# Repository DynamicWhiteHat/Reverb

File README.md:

# Reverb
A custom record player. Place a disk and have it play. Original idea by AKZ Dev on YouTube.

## Features:
- ESP32 S3 Wroom 1 SoM
- 8Ω 10W Speaker
- Disks correspond to songs through an RFID reader
- Gesture sensor for touch-free volume control
- Working stylus that can start and stop music
- 3x8 audio visualizer array
- 2x USB out: 3.0 A at 5V

## Why I designed this project

I saw [this](https://www.youtube.com/watch?v=fBjv4E7mpA4) video on YouTube one day, and I wanted to make my own version. He used an RPi Zero with other modules. I decided that I wanted to improve on this design by making a custom ESP32-based PCB, a built in speaker, and other small features. I also found another video about an ESP32 speaker with an audio visualizer, so I decided to add that through a 3x8 neopixel array. I have gotten better at routing PCBs as a result of this project, and I have also gained a sense of how to make good-looking PCB layouts.

## Image gallery:
<table align="center">
  <tr>
    <td align="center">
      
    </td>
    <td align="center">
      
    </td>
  </tr>
  <tr>
    <td align="center" colspan="2">
      
    </td>
  </tr>
</table>

## Schematic, PCB, And Layout
<table align="center">
  <tr>
    <td align="center" colspan="2">
      
    </td>
  </tr>
  <tr>
    <td align="center">
      
    </td>
    <td align="center">
      
    </td>
  </tr>
  <tr>
    <td align="center" colspan="2">
      
    </td>
  </tr>
  <tr>
    <td align="center" colspan="2">
     
    </td>
  </tr>
</table>

## How It Works
The main control board is based on an ESP32-S3 Wroom 1, which is Wifi and Bluetooth enabled. This allows me to connect the SoM to my phone or other device running Spotify. Using the web API, I can control music that plays from my device. Reverb also uses a MAX98357A I2S amplifier that is wired to an 8Ω 10W speaker, allowing audio playback from the music player instead of the device. Additionally, a 3x8 SK6812 Mini NeoPixel array is mounted on the front of the case with a thin wall, allowing audio playback to be visualized. The PAJ7620U2 gesture sensor, located under the REVERB logo on the case, can detect gestures to increase or decrease volume, skip tracks, and perform other tasks. Finally, the main component in the whole design is the RC522 RFID sensor, which picks up data from the RFID stickers located within the 3D printed disks. This allows each disk to be mapped to a song, allowing playback that feels real.

## Bill Of Materials
| Item                      | Quantity     | Link                                                                                   | Price  | Comment                                            |
|---------------------------|--------------|----------------------------------------------------------------------------------------|--------|----------------------------------------------------|
| JLCPCB Order              | 1            | Quote                                                                                  | $23.62 | PCB+Stencil                                        |
| LCSC Order                | 1            | See LCSC BOM                                                                           | $28.00 | PCB Parts                                          |
| Stepper Motor             | 1            | https://www.aliexpress.us/item/2251832816516054.html                                   | $2.61  |                                                    |
| RC522 RFID Reader         | 1            | https://www.aliexpress.us/item/3256805262944828.html                                   | $1.46  |                                                    |
| RFID Tag                  | 1 Pack of 30 | https://www.aliexpress.us/item/3256807346917359.html                                   | $2.92  |                                                    |
| PAJ7620U2 Gesture Sensor  | 1            | https://www.aliexpress.us/item/3256803918726745.html                                   | $5.09  |                                                    |
| Speaker                   | 1            | https://www.aliexpress.us/item/3256806860528919.html                                   | $8.12  |                                                    |
| Power Switch              | 1 Pack of 5  | https://www.aliexpress.us/item/3256803938436290.html                                   | $2.12  |                                                    |
| SD Card Reader            | 1            | https://www.aliexpress.us/item/3256805115720436.html                                   | $0.83  |                                                    |
| US5881 Hall Effect Sensor | 1 Pack of 10 | https://www.aliexpress.us/item/3256806135616417.html                                   | $1.82  |                                                    |
| M2-M5 Screw Set           | 1            | https://www.amazon.com/mxuteuk-Assortment-Machine-Washers-Printing/dp/B0FM3G5K6H/?th=1 | $9.99  | From Amazon as AliExpress doesn't sell assortments |
|                           |              |                                                                                        | $86.58 |                                                    |

### LCSC Bill Of Materials
| LCSC                                                                                                    |                 |                       |                    |                 |                |          |                                                   |
|---------------------------------------------------------------------------------------------------------|-----------------|-----------------------|--------------------|-----------------|----------------|----------|---------------------------------------------------|
| Description                                                                                             | Quantity Needed | Mrf#                  | Minimum Order Qty. | Unit Price(USD) | Ext.Price(USD) | LCSC#    | Product Link                                      |
| 100nF ±10% 50V Ceramic Capacitor X7R 0603                                                               |              28 | CC0603KRX7R9BB104     |                100 |          0.0021 |           0.21 | C14663   | https://www.lcsc.com/product-detail/C14663.html   |
| 10kΩ ±1% 100mW 0603 Thick Film Resistor                                                                 |               3 | 0603WAF1002T5E        |                100 |          0.0011 |           0.11 | C25804   | https://www.lcsc.com/product-detail/C25804.html   |
| 10uF ±10% 10V Ceramic Capacitor X5R 0603                                                                |               5 | CL10A106KP8NNNC       |                 50 |          0.0065 |           0.33 | C19702   | https://www.lcsc.com/product-detail/C19702.html   |
| 1MΩ ±1% 100mW 0603 Thick Film Resistor                                                                  |               2 | 0603WAF1004T5E        |                100 |          0.0011 |           0.11 | C22935   | https://www.lcsc.com/product-detail/C22935.html   |
| Diode Independent 40V 1A Surface Mount SOD-123                                                          |               1 | K1N5819HW-7-F         |                 50 |          0.0133 |           0.67 | C2891704 | https://www.lcsc.com/product-detail/C2891704.html |
| 1kΩ ±1% 100mW 0603 Thick Film Resistor                                                                  |               1 | 0603WAF1001T5E        |                100 |          0.0012 |           0.12 | C21190   | https://www.lcsc.com/product-detail/C21190.html   |
| 1uF ±10% 50V Ceramic Capacitor X5R 0603                                                                 |               1 | CL10A105KB8NNNC       |                 50 |          0.0056 |           0.28 | C15849   | https://www.lcsc.com/product-detail/C15849.html   |
| 22uF ±20% 6.3V Ceramic Capacitor X5R 0603                                                               |               1 | CL10A226MQ8NRNC       |                 20 |          0.0094 |           0.19 | C59461   | https://www.lcsc.com/product-detail/C59461.html   |
| 4.7kΩ ±1% 100mW 0603 Thick Film Resistor                                                                |               4 | 0603WAF4701T5E        |                100 |          0.0011 |           0.11 | C23162   | https://www.lcsc.com/product-detail/C23162.html   |
| 4.7uF ±10% 16V Ceramic Capacitor X5R 0603                                                               |               2 | CL10A475KO8NNNC       |                 10 |          0.0102 |           0.10 | C19666   | https://www.lcsc.com/product-detail/C19666.html   |
| 5.1kΩ ±1% 100mW 0603 Thick Film Resistor                                                                |               2 | 0603WAF5101T5E        |                100 |          0.0011 |           0.11 | C23186   | https://www.lcsc.com/product-detail/C23186.html   |
| 634kΩ ±1% 100mW 0603 Thick Film Resistor                                                                |               1 | 0603WAF6343T5E        |                100 |          0.0007 |           0.07 | C65831   | https://www.lcsc.com/product-detail/C65831.html   |
| 6V Positive Fixed 3.3V SOT-223 Voltage Regulators - Linear, Low Drop Out (LDO) Regulators RoHS          |               1 | AP7361C-33E-13        |                  5 |          0.2779 |           1.39 | C500795  | https://www.lcsc.com/product-detail/C500795.html  |
| Diode Array 1 Pair Common Cathode 30V 200mA Surface Mount SOT-23                                        |               1 | BAT54C                |                 50 |          0.0095 |           0.48 | C727125  | https://www.lcsc.com/product-detail/C727125.html  |
| Connector Header 2 position 2mm Pitch 2A Right Angle -25℃~+85℃                                          |               1 | S2B-PH-K-S(LF)(SN)    |                 20 |          0.0355 |           0.71 | C173752  | https://www.lcsc.com/product-detail/C173752.html  |
| Connector Header 5 position 2.5mm Pitch 3A Through Hole -25℃~+85℃                                       |               1 | B5B-XH-A(LF)(SN)      |                  5 |          0.0826 |           0.41 | C157991  | https://www.lcsc.com/product-detail/C157991.html  |
| 2.4GHz ESP32-S3 Chip On-board PCB Antenna -98.2dBm SMD,25.5x18mm RF Transceiver Modules and Modems RoHS |               1 | ESP32-S3-WROOM-1-N8R8 |                  1 |          4.9347 |           4.93 | C2913201 | https://www.lcsc.com/product-detail/C2913201.html |
| Class D TQFN-16-EP(3x3) Audio Amplifiers RoHS                                                           |               1 | MAX98357AETE+T        |                  1 |          1.3216 |           1.32 | C910544  | https://www.lcsc.com/product-detail/C910544.html  |
| SMD-4P,3.7x3.5mm LED Addressable, Specialty RoHS                                                        |              24 | SK6812SMINI           |                 30 |          0.0617 |           1.85 | C7423118 | https://www.lcsc.com/product-detail/C7423118.html |
| Tactile Switch SPST 160gf 2mm SMD (SMT) Tab 4mm x 3mm Surface Mount                                     |               2 | TS-1088-AR02016       |                 10 |          0.0426 |           0.43 | C720477  | https://www.lcsc.com/product-detail/C720477.html  |
| Lithium-ion/Polymer ESOP-8                                                                              |               1 | TP4056                |                  5 |           0.091 |           0.46 | C382139  | https://www.lcsc.com/product-detail/C382139.html  |
| 50V 500mA SOIC-16 Bipolar Transistor Arrays RoHS                                                        |               1 | ULN2003ADR            |                  5 |          0.1121 |           0.56 | C7512    | https://www.lcsc.com/product-detail/C7512.html    |
| USB-C (USB TYPE-C) Receptacle Connector 6 Position Surface Mount                                        |               2 | TYPE-C-31-M-17        |                  5 |          0.1789 |           0.89 | C283540  | https://www.lcsc.com/product-detail/C283540.html  |
| USB-C (USB TYPE-C) Receptacle Connector 16 Position Surface Mount                                       |               1 | TYPE-C-31-M-12        |                  5 |          0.1908 |           0.95 | C165948  | https://www.lcsc.com/product-detail/C165948.html  |
| 5kΩ Thin Film Resistor ±25ppm/℃ ±0.1% 0603 Chip Resistor - Surface Mount RoHS                           |               1 | TR0603B5K00P0525Z     |                 20 |           0.028 |           0.56 | C3202451 | https://www.lcsc.com/product-detail/C3202451.html |
| 400mΩ ±1% 100mW 0603 Thick Film Resistor                                                                |               1 | FRL0603FR400TS        |                100 |          0.0035 |           0.35 | C5126047 | https://www.lcsc.com/product-detail/C5126047.html |
|                                                                                                         |                 |                       |                    | Combined Price  |         $18.23 |          |                                                   |
|                                                                                                         |                 |                       |                    | Shipping        |          $9.99 |          |                                                   |
|                                                                                                         |                 |                       |                    | Total Price     |         $27.68 |          |                                                   |

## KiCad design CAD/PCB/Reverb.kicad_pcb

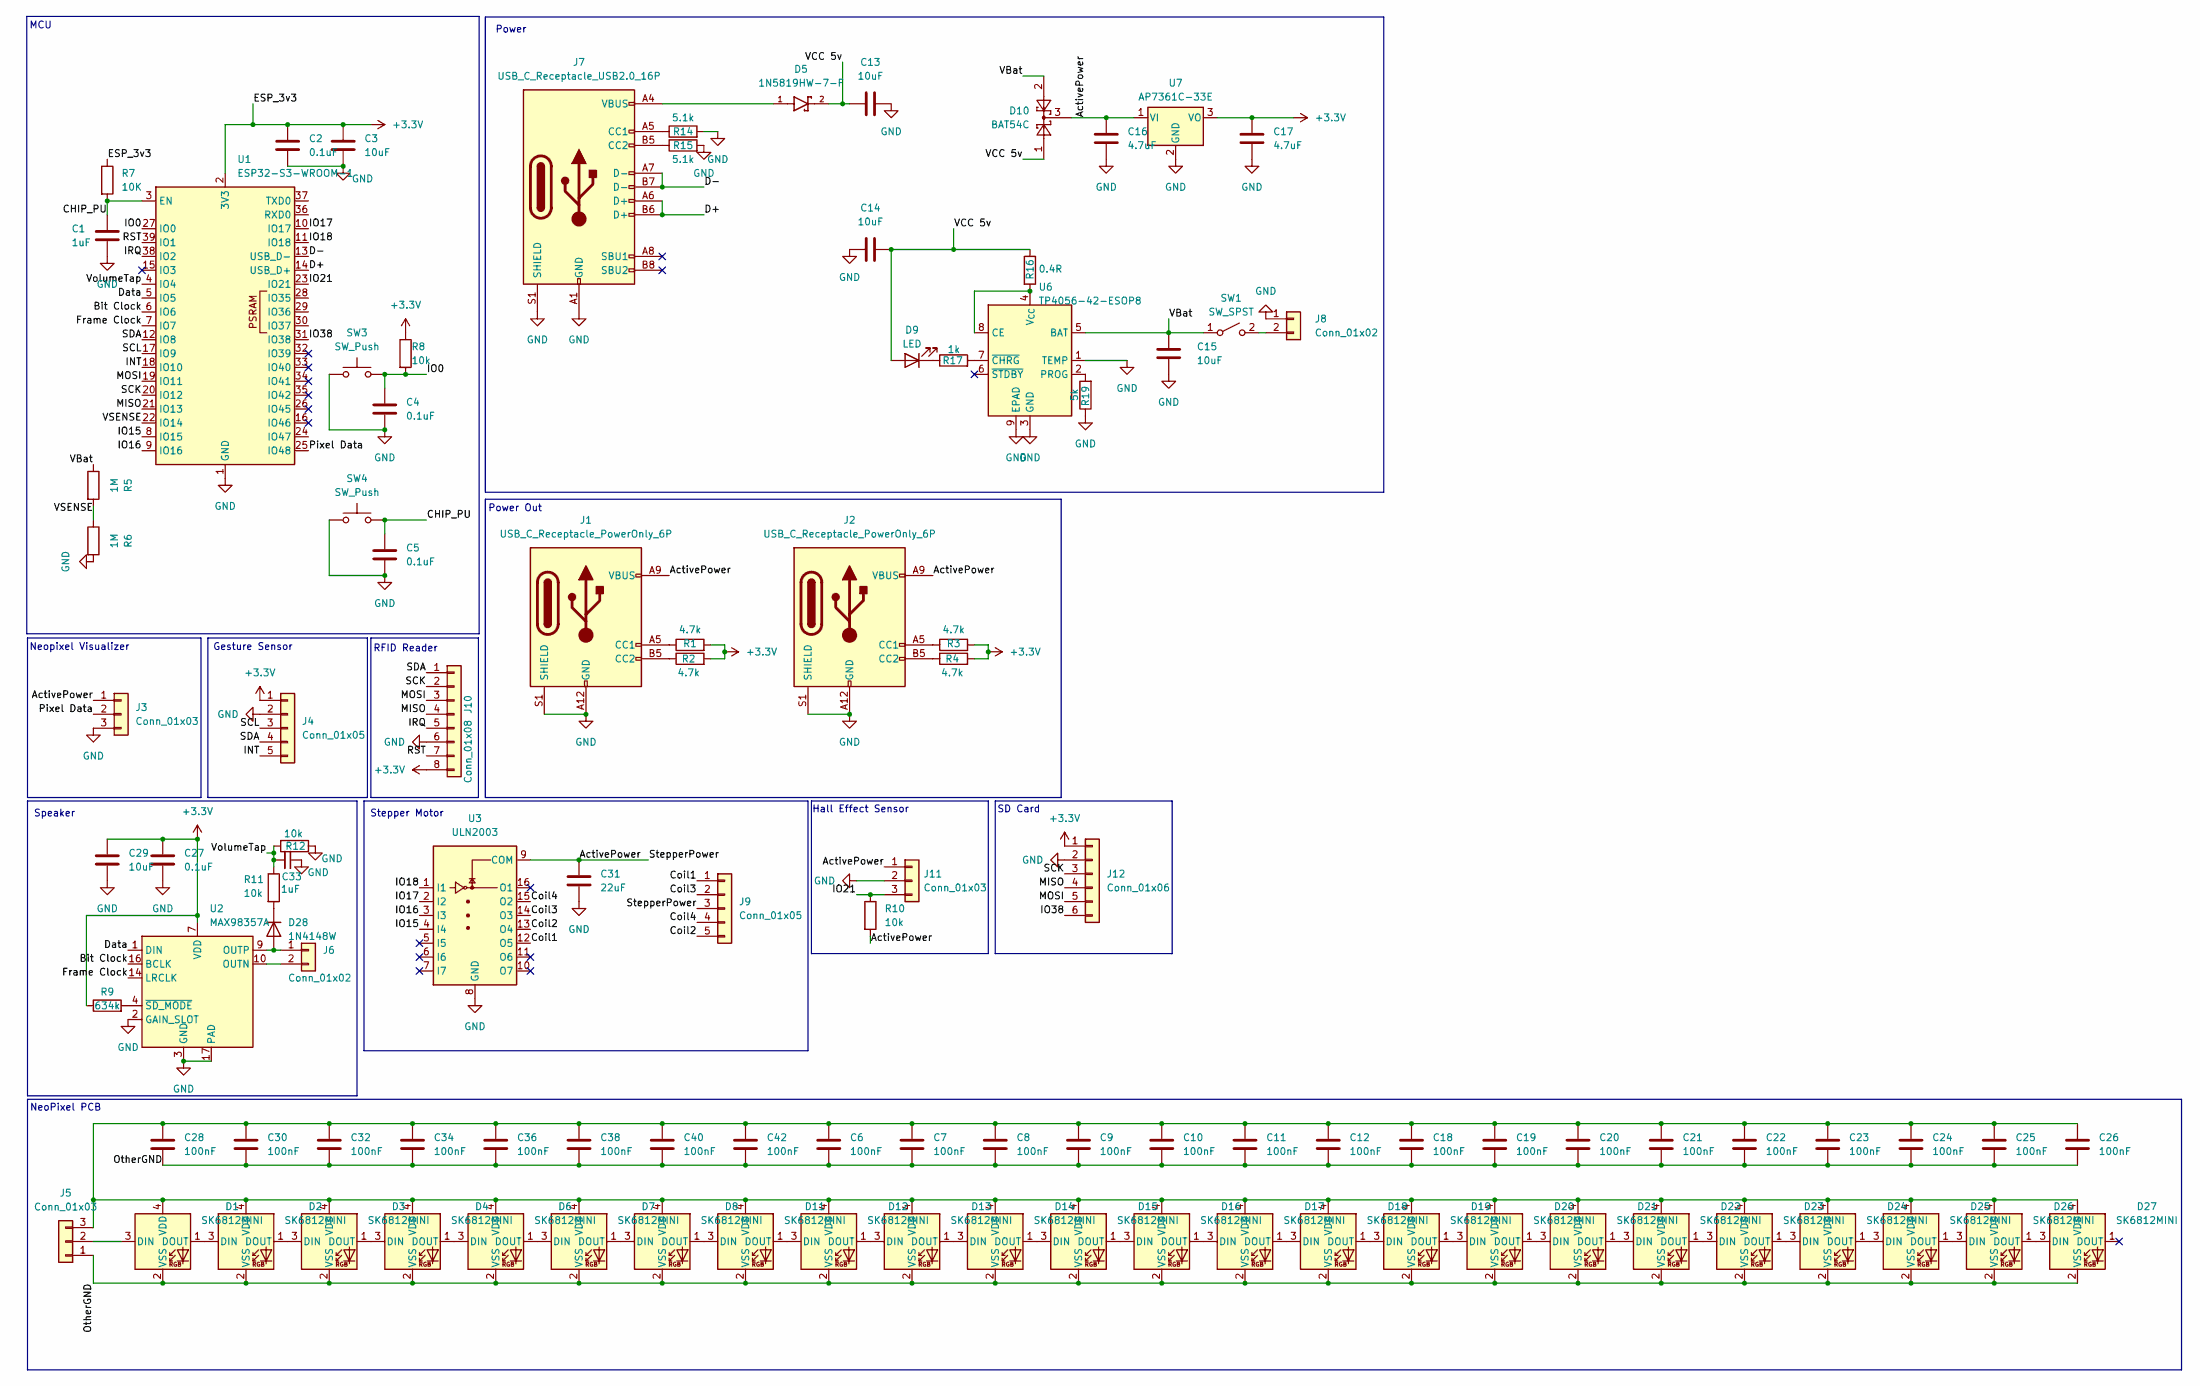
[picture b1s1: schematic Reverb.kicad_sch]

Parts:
C1, C33: 1uF; C_0603_1608Metric
C2, C4, C5, C27: 0.1uF; C_0603_1608Metric
C3, C13, C14, C15, C29: 10uF; C_0603_1608Metric
C6, C7, C8, C9, C10, C11, C12, C18, C19, C20, C21, C22, C23, C24, C25, C26, C28, C30, C32, C34, C36, C38, C40, C42: 100nF; C_0603_1608Metric
C16, C17: 4.7uF; C_0603_1608Metric
C31: 22uF; C_0603_1608Metric
D1, D2, D3, D4, D6, D7, D8, D11, D12, D13, D14, D15, D16, D17, D18, D19, D20, D21, D22, D23, D24, D25, D26, D27: SK6812MINI; LED_SK6812MINI_PLCC4_3.5x3.5mm_P1.75mm
D5: 1N5819HW-7-F; D_SOD-123; PARTREV 18-2
D9: LED; LED_0603_1608Metric
D10: BAT54C; SOT-23
D28: 1N4148W; D_SOD-123
J1, J2: USB_C_Receptacle_PowerOnly_6P; USB_C_Receptacle_HRO_TYPE-C-31-M-17
J3, J5: Conn_01x03; PinHeader_1x03_P2.54mm_Vertical
J4: Conn_01x05; PinHeader_1x05_P2.54mm_Vertical
J6: Conn_01x02; PinHeader_1x02_P2.54mm_Vertical
J7: USB_C_Receptacle_USB2.0_16P; USB_C_Receptacle_HRO_TYPE-C-31-M-12
J8: Conn_01x02; JST_PH_S2B-PH-K_1x02_P2.00mm_Horizontal
J9: Conn_01x05; JST_XH_B5B-XH-AM_1x05_P2.50mm_Vertical
J10: Conn_01x08; PinHeader_1x08_P2.54mm_Vertical
J11: Conn_01x03; PinSocket_1x03_P2.54mm_Vertical
J12: Conn_01x06; 6PinTestPoint_Pad_2.0x2.0mm
R1, R2, R3, R4: 4.7k; R_0603_1608Metric
R5, R6: 1M; R_0603_1608Metric
R7: 10K; R_0603_1608Metric
R8, R10, R11, R12: 10k; R_0603_1608Metric
R9: 634k; R_0603_1608Metric
R14, R15: 5.1k; R_0603_1608Metric
R16: 0.4R; R_0603_1608Metric
R17: 1k; R_0603_1608Metric
R19: 5k; R_0603_1608Metric
SW1: SW_SPST; PinHeader_1x02_P2.54mm_Vertical
SW3, SW4: SW_Push; SW_TS-1088-AR02016
U1: ESP32-S3-WROOM-1
U2: MAX98357A; TQFN-16-1EP_3x3mm_P0.5mm_EP1.23x1.23mm
U3: ULN2003; SOIC-16_3.9x9.9mm_P1.27mm
U6: TP4056-42-ESOP8; SOIC-8-1EP_3.9x4.9mm_P1.27mm_EP2.41x3.3mm_ThermalVias
U7: AP7361C-33E; SOT-223-3_TabPin2

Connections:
+3.3V: C2.1, C3.1, C17.1, C27.1, C29.1, J4.1, J10.8, J12.1, R1.2, R2.2, R3.2, R4.2, R7.1, R8.1, R9.1, U1.2 (3V3), U2.7 (VDD), U2.8 (VDD), U7.3 (VO)
/ActivePower: C16.1, C31.1, D10.3, J1.A9 (VBUS), J1.B9 (VBUS), J2.A9 (VBUS), J2.B9 (VBUS), J3.1, J9.3, J11.1, R10.2, U3.9 (COM), U7.1 (VI)
/Bit Clock: U1.6 (IO6), U2.16 (BCLK)
/CHIP_PU: C1.1, C5.1, R7.2, SW4.2, U1.3 (EN)
/Coil1: J9.1, U3.12 (O5)
/Coil2: J9.5, U3.13 (O4)
/Coil3: J9.2, U3.14 (O3)
/Coil4: J9.4, U3.15 (O2)
/D+: J7.A6 (D+), J7.B6 (D+), U1.14 (USB_D+)
/D-: J7.A7 (D-), J7.B7 (D-), U1.13 (USB_D-)
/Data: U1.5 (IO5), U2.1 (DIN)
/Frame Clock: U1.7 (IO7), U2.14 (LRCLK)
/INT: J4.5, U1.18 (IO10)
/IO0: C4.1, R8.2, SW3.2, U1.27 (IO0)
/IO15: U1.8 (IO15), U3.4 (I4)
/IO16: U1.9 (IO16), U3.3 (I3)
/IO17: U1.10 (IO17), U3.2 (I2)
/IO18: U1.11 (IO18), U3.1 (I1)
/IO21: J11.3, R10.1, U1.23 (IO21)
/IO38: J12.6, U1.31 (IO38)
/IRQ: J10.5, U1.38 (IO2)
/MISO: J10.4, J12.4, U1.21 (IO13)
/MOSI: J10.3, J12.5, U1.19 (IO11)
/OtherGND: C6.2, C7.2, C8.2, C9.2, C10.2, C11.2, C12.2, C18.2, C19.2, C20.2, C21.2, C22.2, C23.2, C24.2, C25.2, C26.2, C28.2, C30.2, C32.2, C34.2, C36.2, C38.2, C40.2, C42.2, D1.2 (VSS), D2.2 (VSS), D3.2 (VSS), D4.2 (VSS), D6.2 (VSS), D7.2 (VSS), D8.2 (VSS), D11.2 (VSS), D12.2 (VSS), D13.2 (VSS), D14.2 (VSS), D15.2 (VSS), D16.2 (VSS), D17.2 (VSS), D18.2 (VSS), D19.2 (VSS), D20.2 (VSS), D21.2 (VSS), D22.2 (VSS), D23.2 (VSS), D24.2 (VSS), D25.2 (VSS), D26.2 (VSS), D27.2 (VSS), J5.1
/Pixel Data: J3.2, U1.25 (IO48)
/RST: J10.7, U1.39 (IO1)
/SCK: J10.2, J12.3, U1.20 (IO12)
/SCL: J4.3, U1.17 (IO9)
/SDA: J4.4, J10.1, U1.12 (IO8)
/VBat: C15.1, D10.2, R5.1, SW1.1 (A), U6.5 (BAT)
/VCC 5v: C13.1, C14.2, D5.2, D9.2 (A), D10.1, R16.1
/VSENSE: R5.2, R6.1, U1.22 (IO14)
/VolumeTap: C33.2, R11.1, R12.2, U1.4 (IO4)
GND: C1.2, C2.2, C3.2, C4.2, C5.2, C13.2, C14.1, C15.2, C16.2, C17.2, C27.2, C29.2, C31.2, C33.1, J1.A12 (GND), J1.B12 (GND), J1.S1 (SHIELD), J2.A12 (GND), J2.B12 (GND), J2.S1 (SHIELD), J3.3, J4.2, J7.A1 (GND), J7.A12 (GND), J7.B1 (GND), J7.B12 (GND), J7.S1 (SHIELD), J8.1, J10.6, J11.2, J12.2, R6.2, R12.1, R14.2, R15.2, R19.1, SW3.1, SW4.1, U1.1 (GND), U1.40 (GND), U1.41 (GND), U2.2 (GAIN_SLOT), U2.3 (GND), U2.11 (GND), U2.15 (GND), U2.17 (PAD), U3.8 (GND), U6.1 (TEMP), U6.3 (GND), U6.9 (EPAD), U7.2 (GND)
unnamed: D1.3 (DIN), J5.2
unnamed: D1.1 (DOUT), D2.3 (DIN)
unnamed: C6.1, C7.1, C8.1, C9.1, C10.1, C11.1, C12.1, C18.1, C19.1, C20.1, C21.1, C22.1, C23.1, C24.1, C25.1, C26.1, C28.1, C30.1, C32.1, C34.1, C36.1, C38.1, C40.1, C42.1, D1.4 (VDD), D2.4 (VDD), D3.4 (VDD), D4.4 (VDD), D6.4 (VDD), D7.4 (VDD), D8.4 (VDD), D11.4 (VDD), D12.4 (VDD), D13.4 (VDD), D14.4 (VDD), D15.4 (VDD), D16.4 (VDD), D17.4 (VDD), D18.4 (VDD), D19.4 (VDD), D20.4 (VDD), D21.4 (VDD), D22.4 (VDD), D23.4 (VDD), D24.4 (VDD), D25.4 (VDD), D26.4 (VDD), D27.4 (VDD), J5.3
unnamed: D2.1 (DOUT), D3.3 (DIN)
unnamed: D3.1 (DOUT), D4.3 (DIN)
unnamed: D4.1 (DOUT), D6.3 (DIN)
unnamed: D5.1, J7.A4 (VBUS), J7.A9 (VBUS), J7.B4 (VBUS), J7.B9 (VBUS)
unnamed: D6.1 (DOUT), D7.3 (DIN)
unnamed: D7.1 (DOUT), D8.3 (DIN)
unnamed: D9.1 (K), R17.1
unnamed: D8.1 (DOUT), D11.3 (DIN)
unnamed: D11.1 (DOUT), D12.3 (DIN)
unnamed: D12.1 (DOUT), D13.3 (DIN)
unnamed: D13.1 (DOUT), D14.3 (DIN)
unnamed: D14.1 (DOUT), D15.3 (DIN)
unnamed: D15.1 (DOUT), D16.3 (DIN)
unnamed: D16.1 (DOUT), D17.3 (DIN)
unnamed: D17.1 (DOUT), D18.3 (DIN)
unnamed: D18.1 (DOUT), D19.3 (DIN)
unnamed: D19.1 (DOUT), D20.3 (DIN)
unnamed: D20.1 (DOUT), D21.3 (DIN)
unnamed: D21.1 (DOUT), D22.3 (DIN)
unnamed: D22.1 (DOUT), D23.3 (DIN)
unnamed: D23.1 (DOUT), D24.3 (DIN)
unnamed: D24.1 (DOUT), D25.3 (DIN)
unnamed: D25.1 (DOUT), D26.3 (DIN)
unnamed: D26.1 (DOUT), D27.3 (DIN)
unnamed: D28.2 (A), J6.1, U2.9 (OUTP)
unnamed: D28.1 (K), R11.2
unnamed: J1.A5 (CC1), R1.1
unnamed: J1.B5 (CC2), R2.1
unnamed: J2.A5 (CC1), R3.1
unnamed: J2.B5 (CC2), R4.1
unnamed: J6.2, U2.10 (OUTN)
unnamed: J7.A5 (CC1), R14.1
unnamed: J7.B5 (CC2), R15.1
unnamed: J8.2, SW1.2 (B)
unnamed: R9.2, U2.4 (~SD_MODE)
unnamed: R16.2, U6.4 (V_{CC}), U6.8 (CE)
unnamed: R19.2, U6.2 (PROG)
unnamed: R17.2, U6.7 (~CHRG)

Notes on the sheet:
Neopixel Visualizer
Power Out
SD Card
NeoPixel PCB
MCU
Stepper Motor
Power
Hall Effect Sensor
Speaker
RFID Reader
Gesture Sensor

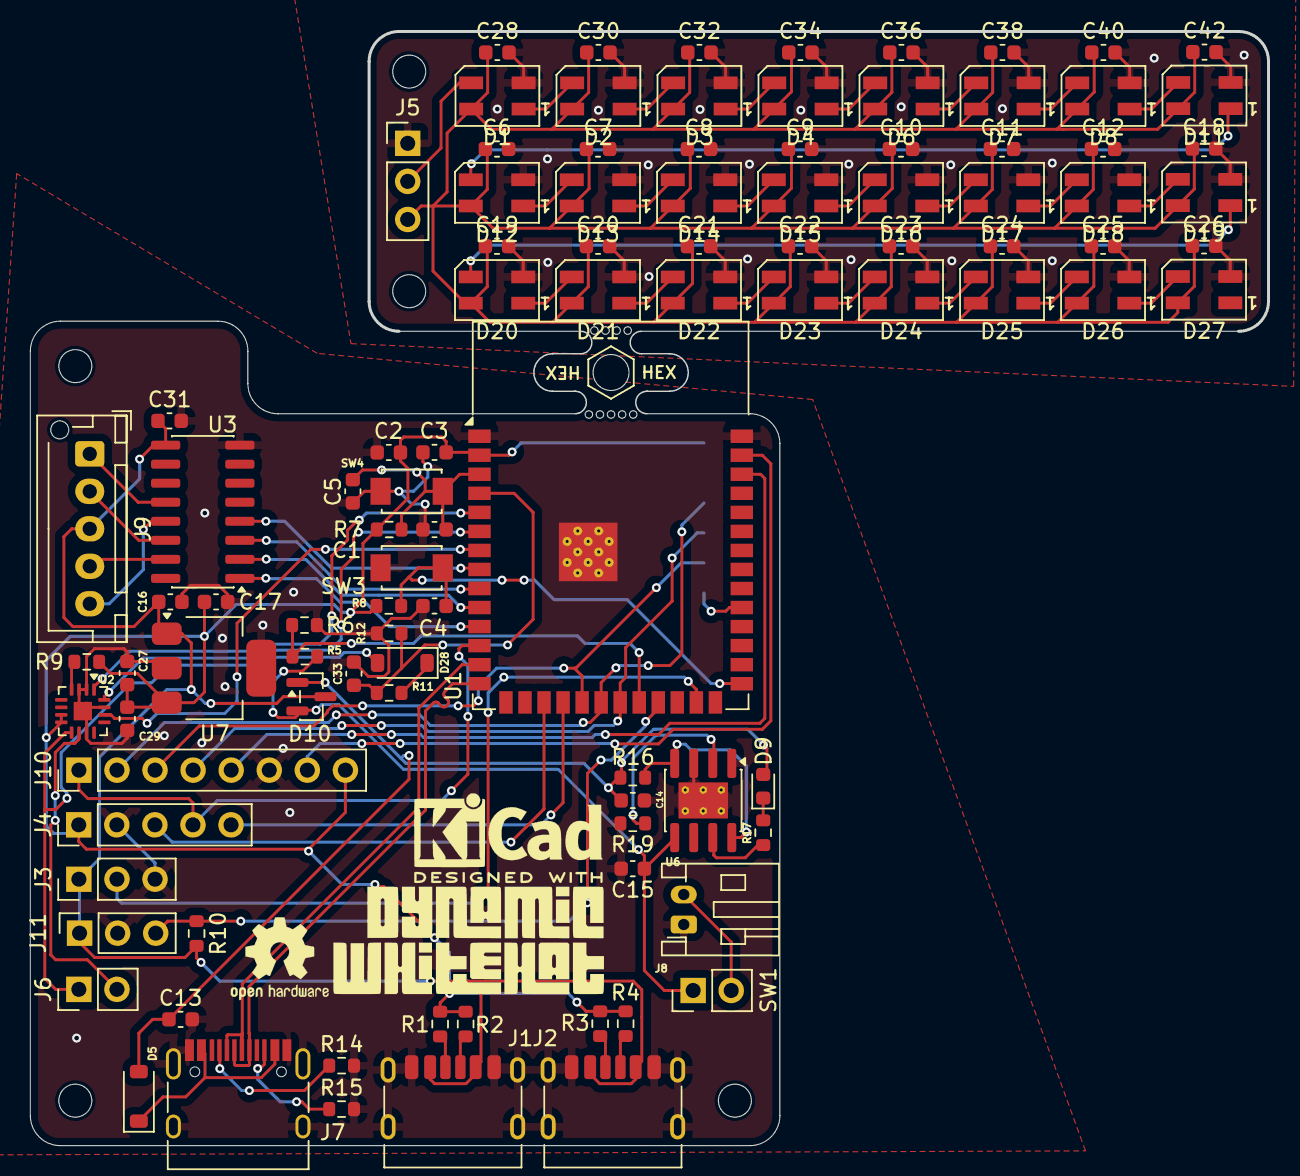
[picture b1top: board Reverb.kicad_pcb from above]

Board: 2 copper layers, 82.5 x 74.2 mm, 104 parts (1 on the bottom side), 75 nets.

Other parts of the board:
MB5: 5.5mm; mousebites_5p5mm_easysnap

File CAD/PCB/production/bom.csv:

Designator,Footprint,Quantity,Value,LCSC Part #
C1,0603,1,1uF,C15849
"C10, C11, C12, C18, C19, C20, C21, C22, C23, C24, C25, C26, C28, C30, C32, C34, C36, C38, C40, C42, C6, C7, C8, C9",0603,24,100nF,C14663
"C13, C14, C15, C29, C3",0603,5,10uF,C19702
"C16, C17",0603,2,4.7uF,C19666
"C2, C27, C4, C5",0603,4,0.1uF,C14663
C31,0603,1,22uF,C59461
C33,0603,1,1uF,
"D1, D11, D12, D13, D14, D15, D16, D17, D18, D19, D2, D20, D21, D22, D23, D24, D25, D26, D27, D3, D4, D6, D7, D8",LED_SK6812MINI_PLCC4_3.5x3.5mm_P1.75mm,24,SK6812MINI,C7423118
D10,SOT-23,1,BAT54C,C727125
D28,D_SOD-123,1,1N4148W,
D5,D_SOD-123,1,1N5819HW-7-F,C2891704
D9,0603,1,LED,C2286
"J1, J2",USB_C_Receptacle_HRO_TYPE-C-31-M-17,2,USB_C_Receptacle_PowerOnly_6P,C283540
J10,PinHeader_1x08_P2.54mm_Vertical,1,Conn_01x08,
J11,PinSocket_1x03_P2.54mm_Vertical,1,Conn_01x03,
J12,6PinTestPoint_Pad_2.0x2.0mm,1,Conn_01x06,
"J3, J5",PinHeader_1x03_P2.54mm_Vertical,2,Conn_01x03,
J4,PinHeader_1x05_P2.54mm_Vertical,1,Conn_01x05,
J6,PinHeader_1x02_P2.54mm_Vertical,1,Conn_01x02,
J7,USB_C_Receptacle_HRO_TYPE-C-31-M-12,1,USB_C_Receptacle_USB2.0_16P,C9900184415
J8,JST_PH_S2B-PH-K_1x02_P2.00mm_Horizontal,1,Conn_01x02,C173752
J9,JST_XH_B5B-XH-AM_1x05_P2.50mm_Vertical,1,Conn_01x05,C157991
"R1, R2, R3, R4",0603,4,4.7k,C23162
"R10, R7, R8",0603,3,10k,C25804
"R11, R12",0603,2,10k,
"R14, R15",0603,2,5.1k,C23186
R16,0603,1,0.4R,
R17,0603,1,1k,C21190
R19,0603,1,5k,
"R5, R6",0603,2,1M,C22935
R9,0603,1,634k,C65831
SW1,PinHeader_1x02_P2.54mm_Vertical,1,SW_SPST,
"SW3, SW4",SW_TS-1088-AR02016,2,SW_Push,C720477
U1,ESP32-S3-WROOM-1,1,ESP32-S3-WROOM-1,C2913198
U2,TQFN-16-1EP_3x3mm_P0.5mm_EP1.23x1.23mm,1,MAX98357A,C910544
U3,SOIC-16_3.9x9.9mm_P1.27mm,1,ULN2003,C7512
U6,SOIC-8-1EP_3.9x4.9mm_P1.27mm_EP2.41x3.3mm_ThermalVias,1,TP4056-42-ESOP8,C382139
U7,SOT-223-3_TabPin2,1,AP7361C-33E,C500795

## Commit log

2026-01-24 Added files
2026-01-24 Added images
2026-01-24 Added Back
2026-01-24 Made transparent files
2026-01-24 Update Reverb1T.png asset
2026-01-24 Update README with project details and BOM
    Expanded project description, added features, and included bill of materials with links and prices.
2026-01-24 Update BOM prices and ESP32 chip details
    Updated prices for LCSC order items and corrected ESP32 chip reference.
2026-01-24 Update prices and add new items in BOM
2026-01-24 Added code
2026-01-24 Revise quantities and prices in README BOM
    Updated quantities and prices for several components in the BOM.
2026-01-24 Adjust prices and quantities in Reverb BOM
    Updated prices for Power Switch, SD Card Reader, and US5881 Hall Effect Sensor.
2026-01-25 Update LCSC order details in README
    Updated LCSC order prices and quantities in the Bill of Materials section.
2026-01-25 Revise component prices and totals in BOM
    Updated prices and quantities for various components in the BOM.
2026-01-25 Revise BOM with new components and pricing
    Updated component list and prices, added LCSC items.
2026-02-04 Update JLCPCB Order price in README
    Updated the price for JLCPCB Order and total cost in the Bill Of Materials.
2026-02-04 Modify JLCPCB order price and total in BOM
    Updated JLCPCB order price and total cost in BOM.
2026-02-12 Revise BOM quantities and prices in README.md
    Updated quantities and prices for various items in the Bill Of Materials section.
2026-02-12 Revise component prices and links in BOM
    Updated prices and links for various components in the BOM.
2026-02-12 Add image to README for enhanced visual content
    Added an image to the README for better visualization.
